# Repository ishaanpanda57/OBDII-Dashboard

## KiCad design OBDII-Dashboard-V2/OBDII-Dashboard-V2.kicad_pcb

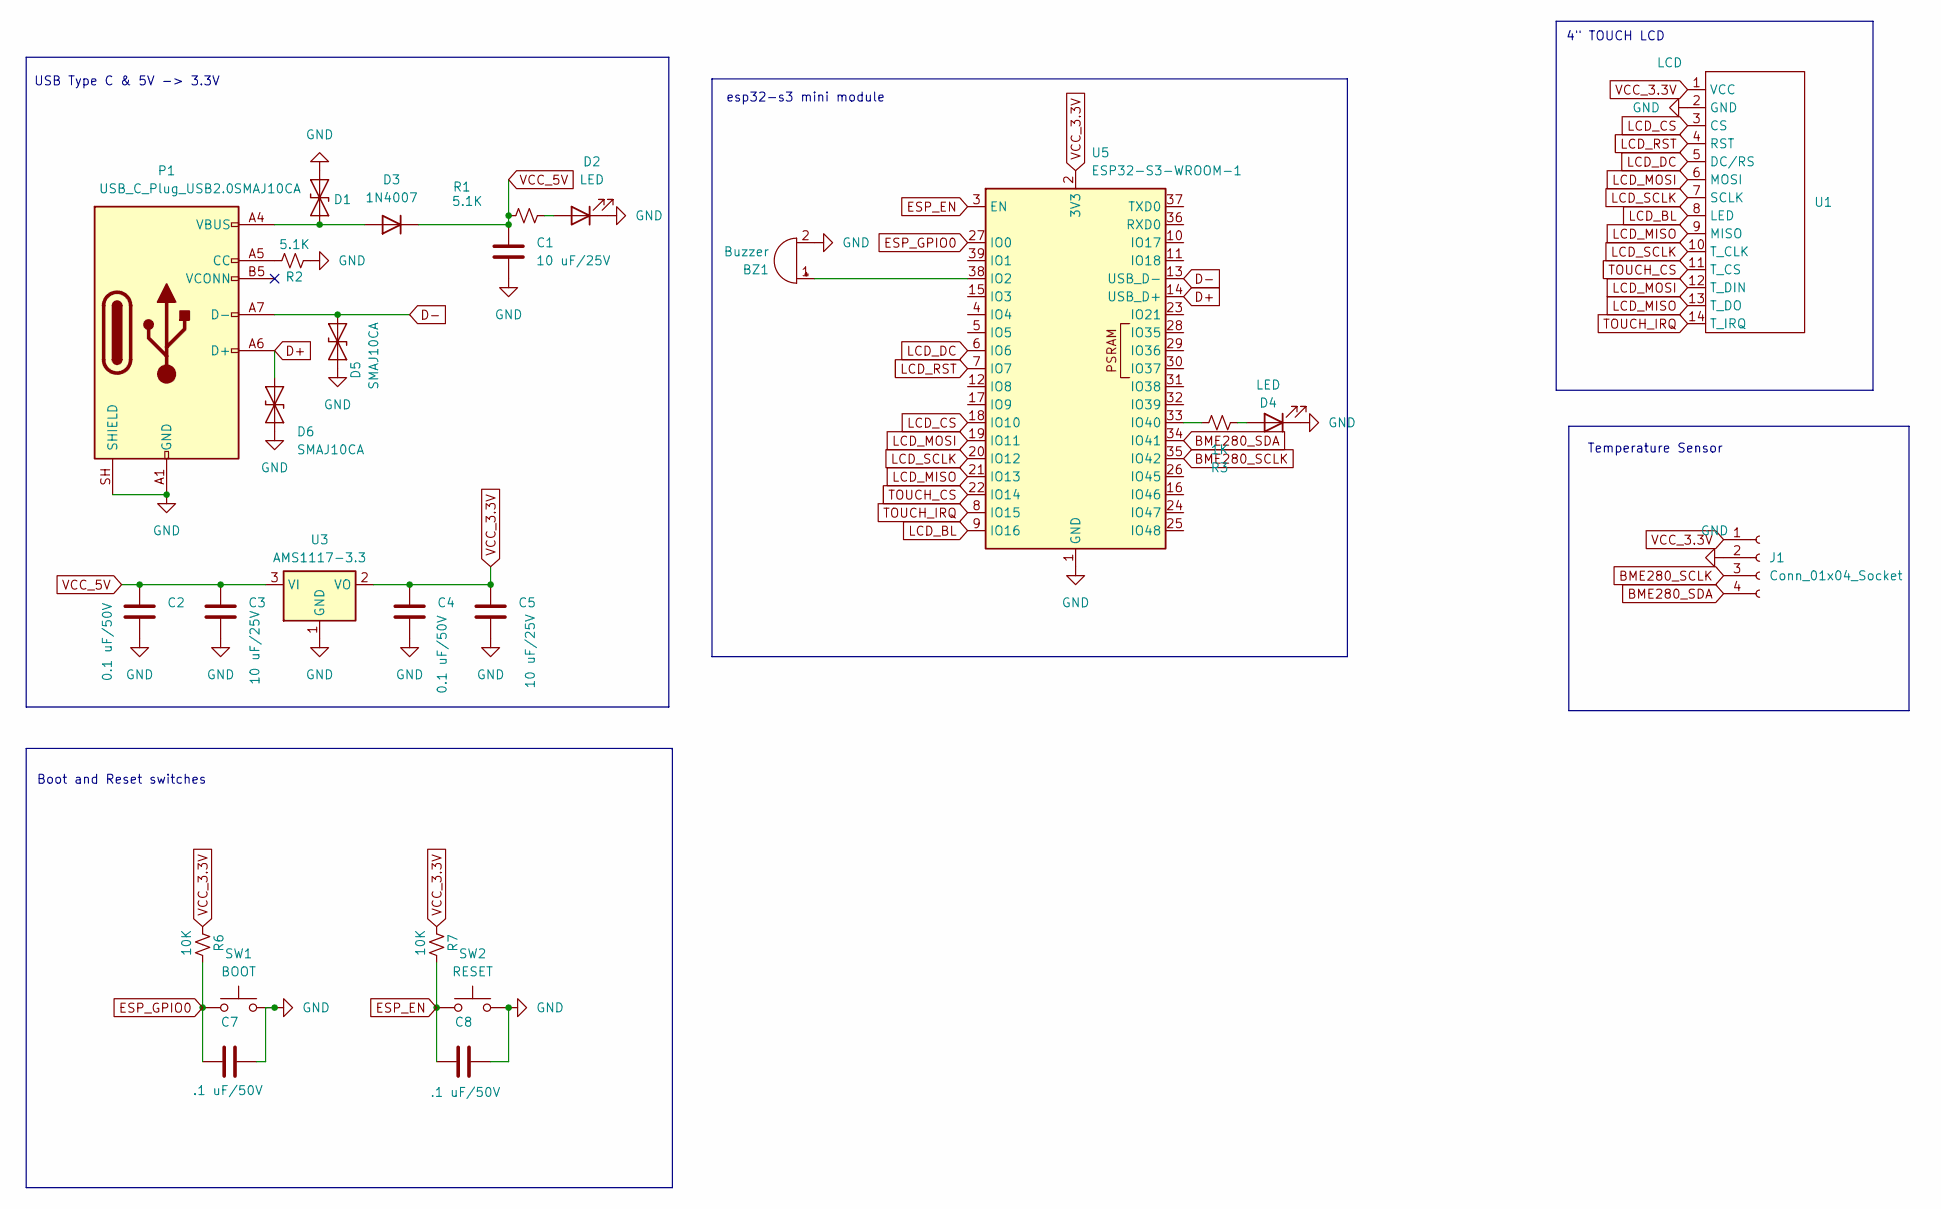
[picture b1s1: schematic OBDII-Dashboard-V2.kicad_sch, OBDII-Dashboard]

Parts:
BZ1: Buzzer; PUIAudio_SMT_0825_S_4_R
C1, C3, C5: 10 uF/25V; C_0805_2012Metric
C2, C4: 0.1 uF/50V; C_0805_2012Metric
C7, C8: .1 uF/50V; C_0805_2012Metric
D1, D5, D6: SMAJ10CA; D_SMA
D2, D4: LED; LED_0805_2012Metric
D3: 1N4007; D_SMA
J1: Conn_01x04_Socket; PinSocket_1x04_P2.54mm_Vertical
P1: USB_C_Plug_USB2.0; USB_C_Receptacle_GCT_USB4105-xx-A_16P_TopMnt_Horizontal
R1, R2: 5.1K; R_0805_2012Metric_Pad1.20x1.40mm_HandSolder
R3: 1K; R_0805_2012Metric_Pad1.20x1.40mm_HandSolder
R6, R7: 10K; R_0805_2012Metric_Pad1.20x1.40mm_HandSolder
SW1: BOOT; SW_Push_1P1T_NO_CK_KSC9xxG
SW2: RESET; SW_Push_1P1T_NO_CK_KSC9xxG
U1: LCD; PinHeader_1x14_P2.54mm_Vertical
U3: AMS1117-3.3; SOT-223-3_TabPin2
U5: ESP32-S3-WROOM-1

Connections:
BME280_SCLK: J1.3, U5.35 (IO42)
BME280_SDA: J1.4, U5.34 (IO41)
D+: D6.2 (A2), P1.A6 (D+), U5.14 (USB_D+)
D-: D5.2 (A2), P1.A7 (D-), U5.13 (USB_D-)
ESP_EN: C8.1, R7.2, SW2.1, U5.3 (EN)
ESP_GPIO0: C7.1, R6.2, SW1.1, U5.27 (IO0)
GND: BZ1.2 (-), C1.2, C2.2, C3.2, C4.2, C5.2, C7.2, C8.2, D1.1 (A1), D2.1 (K), D4.1 (K), D5.1 (A1), D6.1 (A1), J1.2, P1.A1 (GND), P1.A12 (GND), P1.B1 (GND), P1.B12 (GND), P1.SH (SHIELD), R2.1, SW1.2, SW2.2, U1.2 (GND), U3.1 (GND), U5.1 (GND), U5.40 (GND), U5.41 (GND)
LCD_BL: U1.8 (LED), U5.9 (IO16)
LCD_CS: U1.3 (CS), U5.18 (IO10)
LCD_DC: U1.5 (DC/RS), U5.6 (IO6)
LCD_MISO: U1.9 (MISO), U1.13 (T_DO), U5.21 (IO13)
LCD_MOSI: U1.6 (MOSI), U1.12 (T_DIN), U5.19 (IO11)
LCD_RST: U1.4 (RST), U5.7 (IO7)
LCD_SCLK: U1.7 (SCLK), U1.10 (T_CLK), U5.20 (IO12)
unnamed: BZ1.1 (+), U5.38 (IO2)
unnamed: D1.2 (A2), D3.2 (A), P1.A4 (VBUS), P1.A9 (VBUS), P1.B4 (VBUS), P1.B9 (VBUS)
unnamed: D2.2 (A), R1.1
unnamed: D4.2 (A), R3.1
unnamed: P1.A5 (CC), R2.2
unnamed: R3.2, U5.33 (IO40)
TOUCH_CS: U1.11 (T_CS), U5.22 (IO14)
TOUCH_IRQ: U1.14 (T_IRQ), U5.8 (IO15)
VCC_3.3V: C4.1, C5.1, J1.1, R6.1, R7.1, U1.1 (VCC), U3.2 (VO), U5.2 (3V3)
VCC_5V: C1.1, C2.1, C3.1, D3.1 (K), R1.2, U3.3 (VI)

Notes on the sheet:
4" TOUCH LCD
Temperature Sensor
Boot and Reset switches
esp32-s3 mini module
USB Type C & 5V -> 3.3V

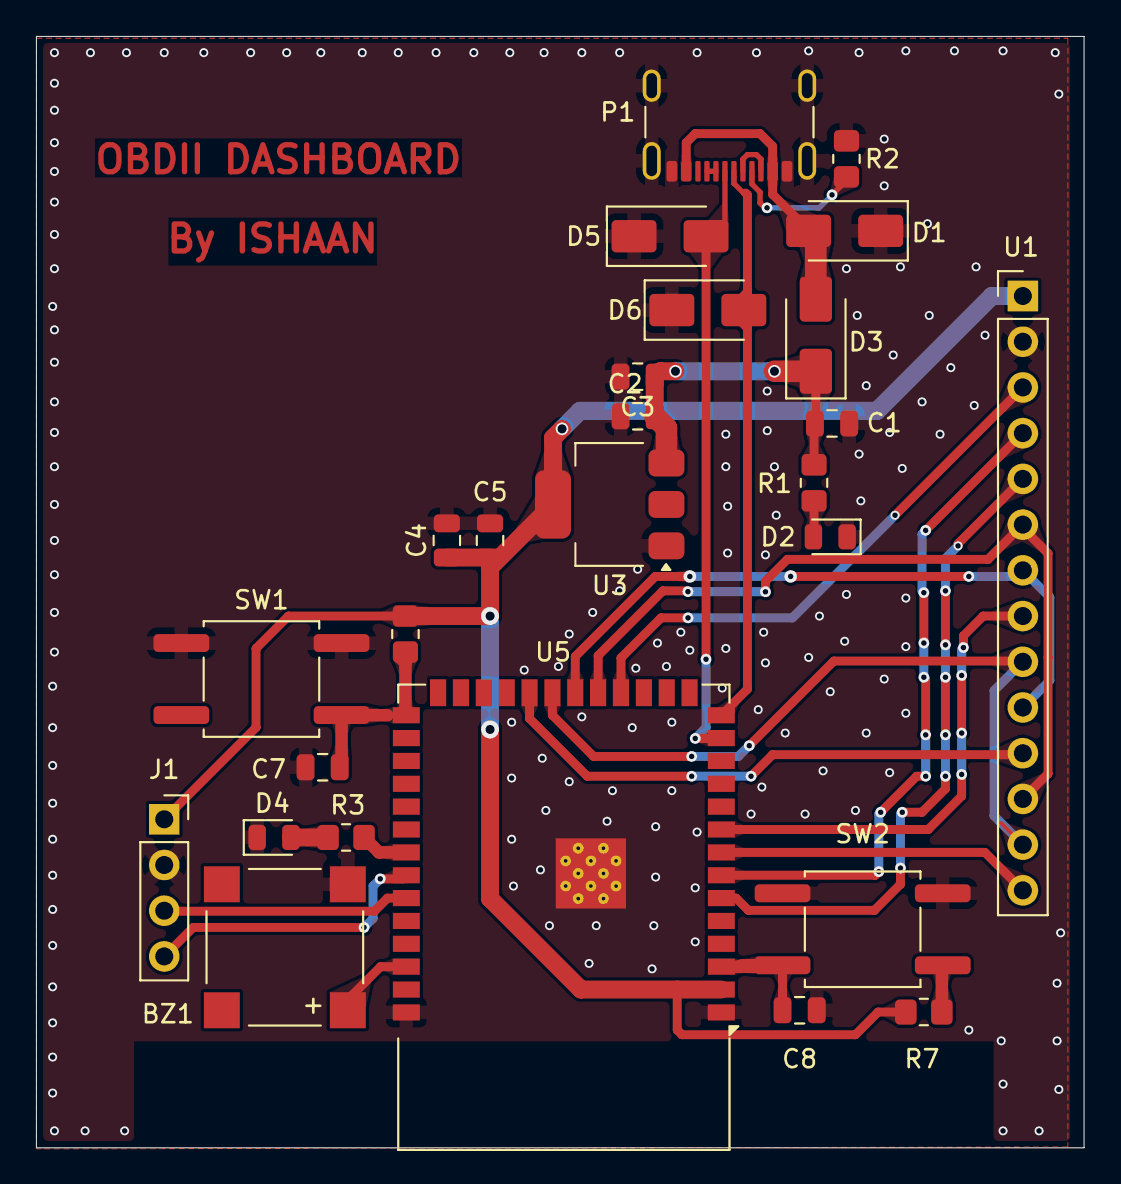
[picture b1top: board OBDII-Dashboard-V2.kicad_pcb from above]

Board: 2 copper layers, 58.2 x 61.7 mm, 26 parts (0 on the bottom side), 24 nets.
